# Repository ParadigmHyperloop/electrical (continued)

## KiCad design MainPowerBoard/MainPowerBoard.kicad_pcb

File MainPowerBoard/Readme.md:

# Main Power Board
This board provides approriate conversion of power from 120/240VAC and 37V nominal battery packs and distribution to both 24V and 5V system loads (all loads).

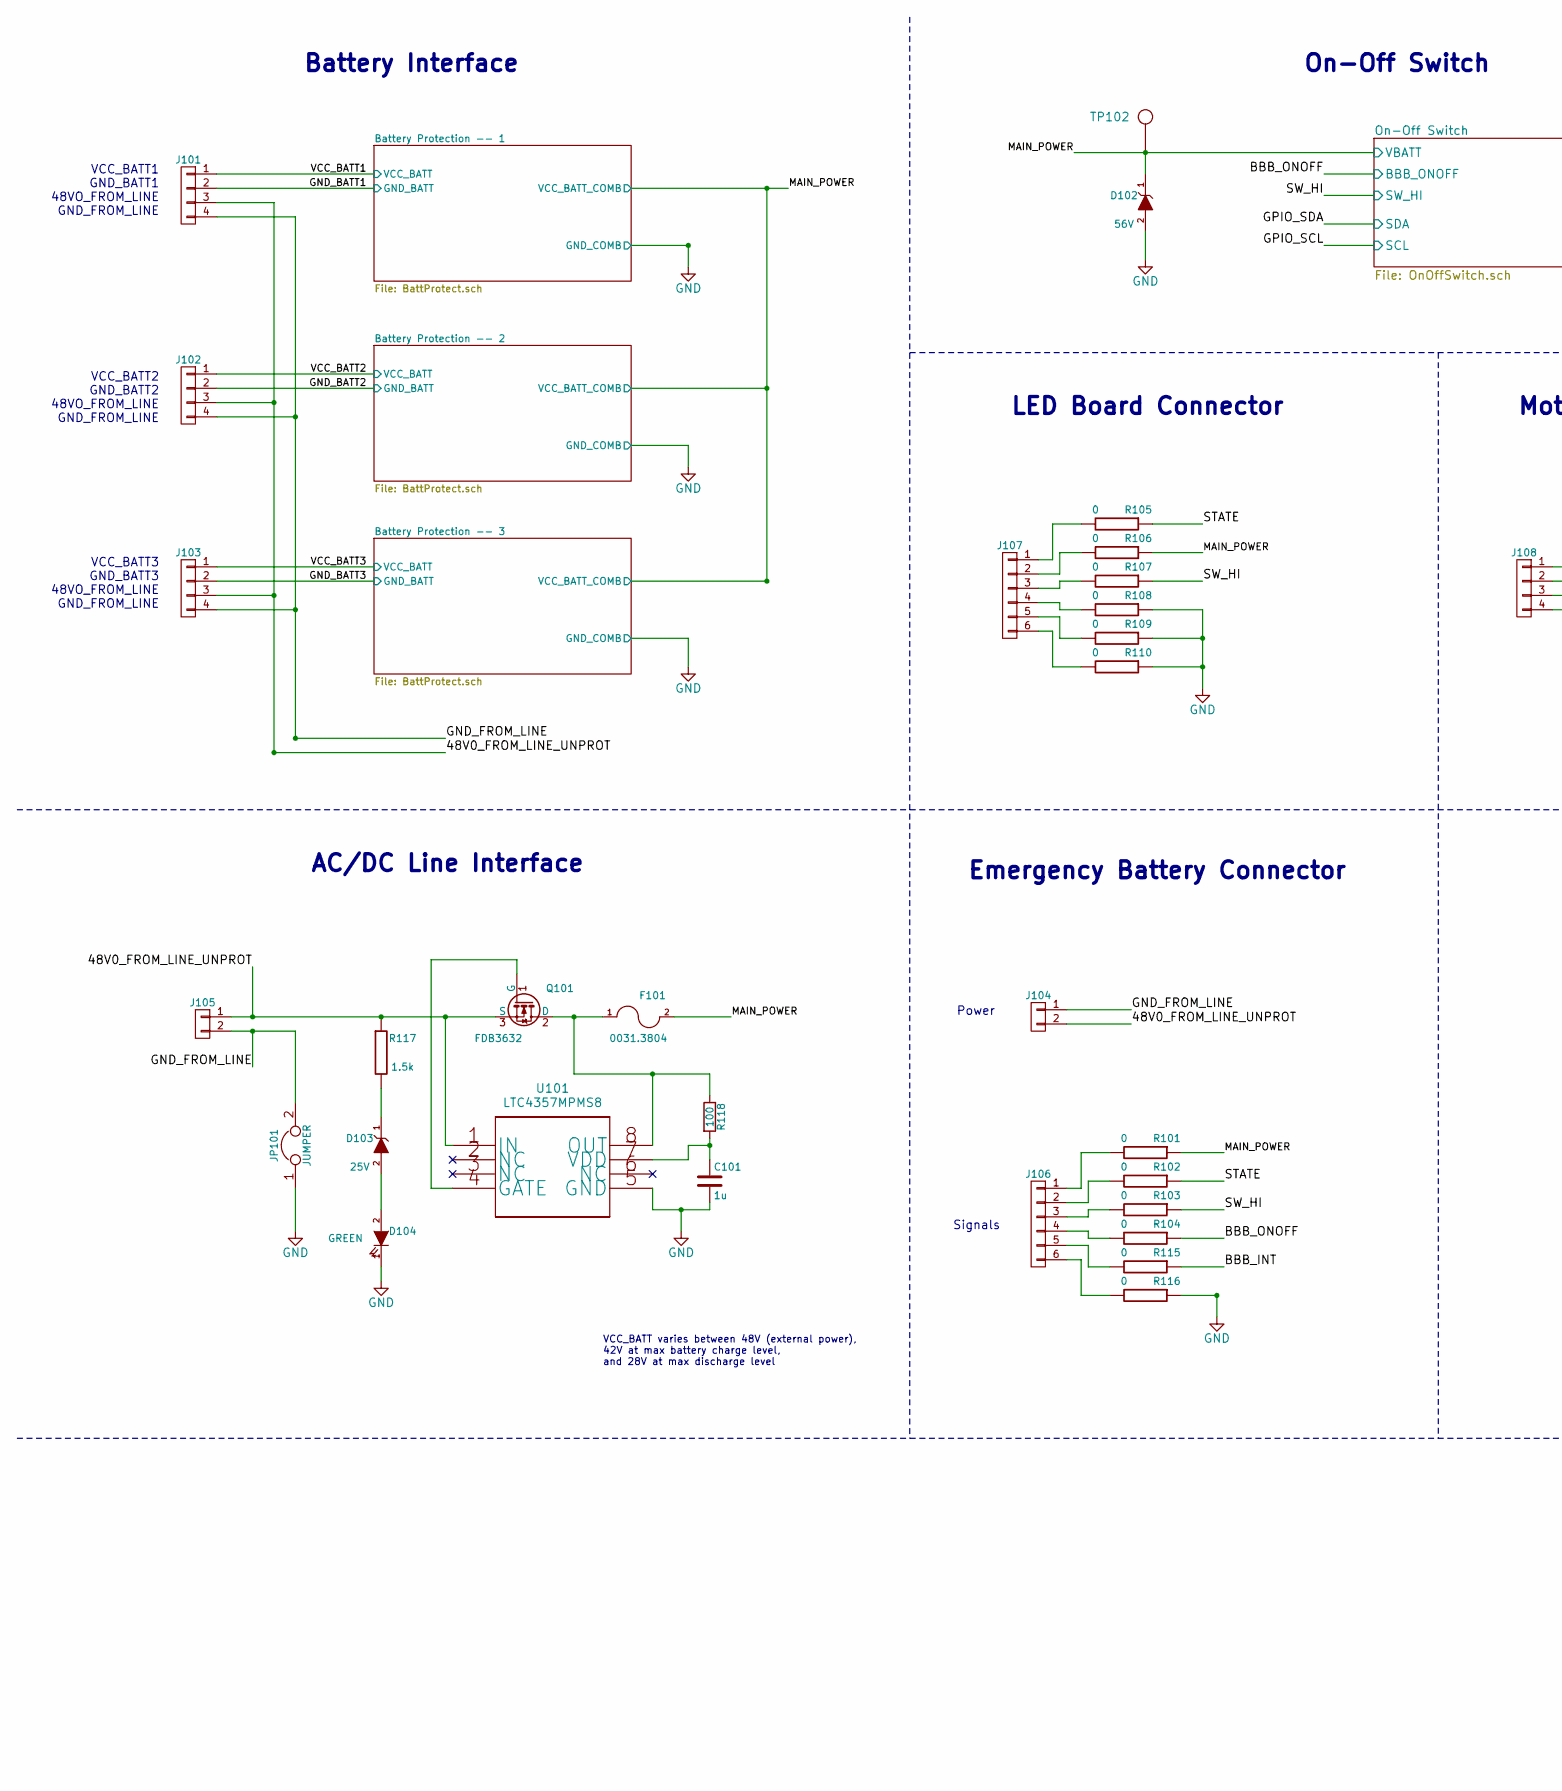
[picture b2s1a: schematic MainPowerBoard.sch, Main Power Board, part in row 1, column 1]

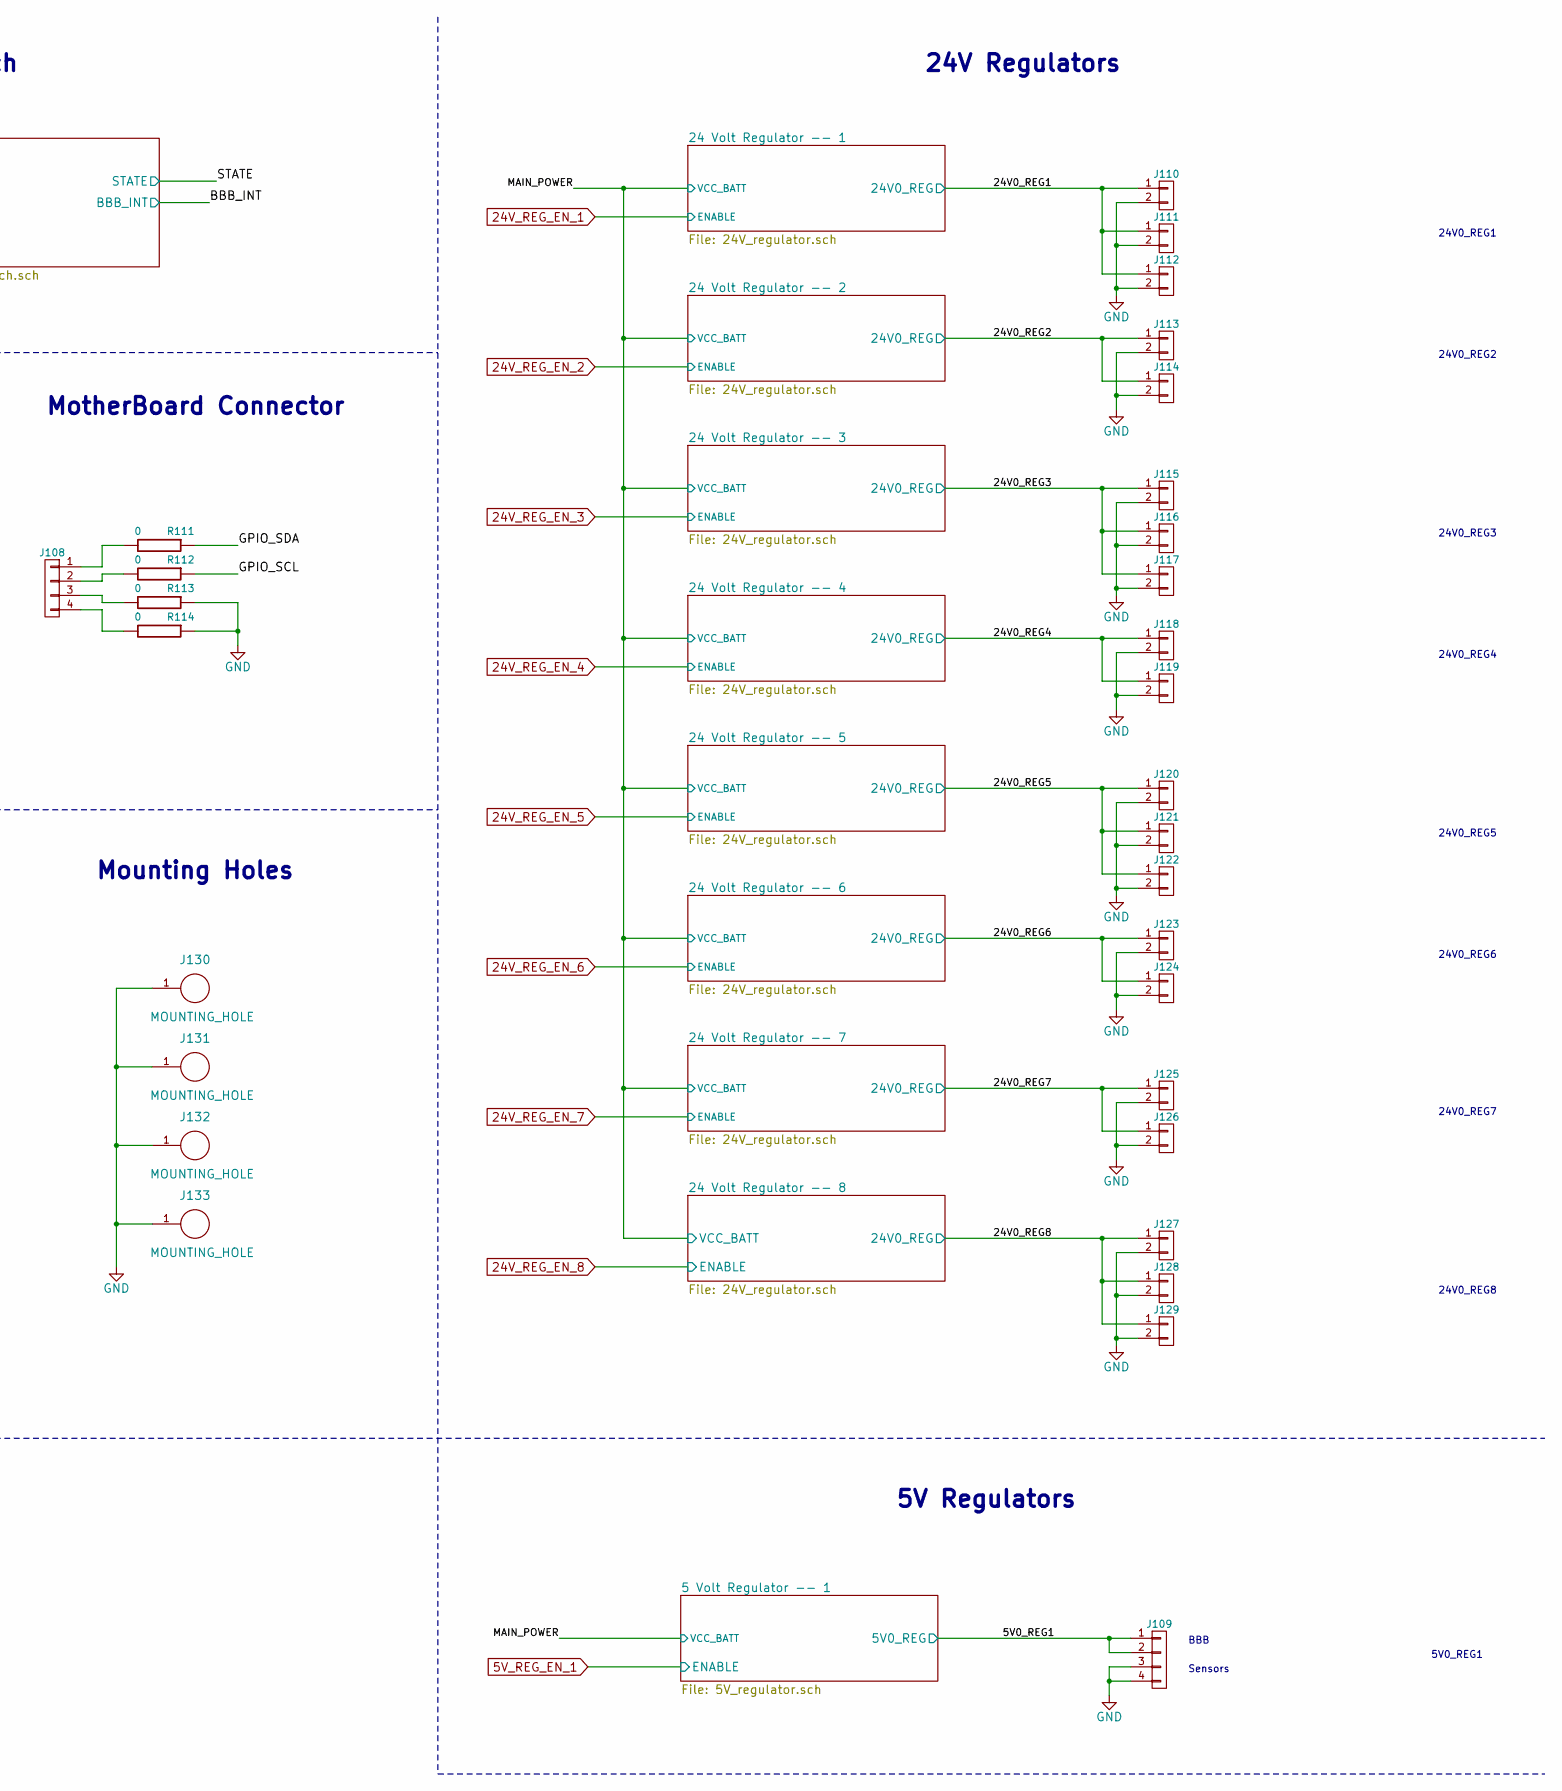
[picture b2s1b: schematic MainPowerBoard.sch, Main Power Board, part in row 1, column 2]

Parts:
C101: 1u; C_0805_HandSoldering; Voltage Rating 100V; Mfg. PN GRJ21BC72A105KE11L; DigiKey PN 490-10918-1-ND
D102: 56V; SMB_Handsoldering; Mfg. PN SMBJ5370B-TP; DigiKey PN SMBJ5370B-TPMSCT-ND
D103: 25V; SOD-123; Mfg. PN MMSZ5253BT1G; DigiKey PN MMSZ5253BT1GOSCT-ND
D104: GREEN; LED_1206; Mfg. PN APT3216LZGCK; DigiKey PN 754-1944-1-ND
F101: 0031.3804; SCHURTER_0031_3804_FUSE; Mfg. PN 0031.3804; DigiKey PN 486-1754-ND
J101, J102, J103, J108, J109: CONN_01X04; CONN_PHOENIX_1844236_4PIN_1; Mfg. PN 1844236; DigiKey PN 277-2419-ND
J104, J110, J111, J112, J113, J114, J115, J116, J117, J118, J119, J120, J121, J122, J123, J124, J125, J126, J127, J128, J129: CONN_01X02; CONN_PHOENIX_1844210_2PIN; Mfg. PN 1844210; DigiKey PN 277-2416-ND
J105: CONN_01X02; CONN_PHOENIX_1720466_2PIN; Mfg. PN 1720466; DigiKey PN 277-6070-ND
J106, J107: CONN_01X06; CONN_PHOENIX_1844252_6PIN; Mfg. PN 1844252; Digikey PN 277-2427-ND
J130, J131, J132, J133: MOUNTING_HOLE; MountingHole_5.5mm_Pad_Via
JP101: JUMPER; R_2512_HandSoldering; Mfg. PN HCJ2512ZT0R00; DigiKey PN HCJ2512ZT0R00CT-ND
Q101: FDB3632; TO-263-2; Mfg. PN FDB3632; Digikey PN FDB3632CT-ND
R101, R102, R103, R104, R105, R106, R107, R108, R109, R110, R111, R112, R113, R114, R115, R116: 0; R_1206_HandSoldering; Mfg. PN RC1206JR-070RL; DigiKey PN 311-0.0ERCT-ND
R117: 1.5k; R_1206_HandSoldering; Mfg. PN ERJ-P08J152V; DigiKey PN P1.5KALCT-ND
R118: 100; R_0603_HandSoldering; Power Rating 3.9W; Mfg. PN RCP0603W100RGEB; DigiKey PN 541-2653-1-ND
TP102: Testpoint; TP_SMT_Keystone; Mfg. PN 5018; DigiKey PN 36-5018CT-ND
U101: LTC4357MPMS8; MSOP-8_3x3mm_Pitch0.65mm; Mfg. PN LTC4357HMS8#PBF; DigiKey PN LTC4357HMS8#PBF-ND

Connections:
/5V0_REG1: J109.1, J109.2; also elsewhere on the board
/24V0_REG1: J110.1, J111.1, J112.1; also elsewhere on the board
/24V0_REG2: J113.1, J114.1; also elsewhere on the board
/24V0_REG3: J115.1, J116.1, J117.1; also elsewhere on the board
/24V0_REG4: J118.1, J119.1; also elsewhere on the board
/24V0_REG5: J120.1, J121.1, J122.1; also elsewhere on the board
/24V0_REG6: J123.1, J124.1; also elsewhere on the board
/24V0_REG7: J125.1, J126.1; also elsewhere on the board
/24V0_REG8: J127.1, J128.1, J129.1; also elsewhere on the board
/48V0_FROM_LINE_UNPROT: J101.3, J102.3, J103.3, J104.2, J105.1, Q101.3 (S), R117.1, U101.1 (IN)
/BBB_INT: R115.1; also elsewhere on the board
/BBB_ONOFF: R104.1; also elsewhere on the board
/GND_FROM_LINE: J101.4, J102.4, J103.4, J104.1, J105.2, JP101.2
/GPIO_SCL: R112.1; also elsewhere on the board
/GPIO_SDA: R111.1; also elsewhere on the board
/MAIN_POWER: D102.1 (A), F101.2, R101.1, R106.1, TP102.~; also elsewhere on the board
/STATE: R102.1, R105.1; also elsewhere on the board
/SW_HI: R103.1, R107.1; also elsewhere on the board
/VCC_BATT1: J101.1; also elsewhere on the board
/VCC_BATT2: J102.1; also elsewhere on the board
/VCC_BATT3: J103.1; also elsewhere on the board
GND: C101.2, D102.2 (K), D104.1 (A), J101.2, J102.2, J103.2, J109.3, J109.4, J110.2, J111.2, J112.2, J113.2, J114.2, J115.2, J116.2, J117.2, J118.2, J119.2, J120.2, J121.2, J122.2, J123.2, J124.2, J125.2, J126.2, J127.2, J128.2, J129.2, J130.1, J131.1, J132.1, J133.1, JP101.1, R108.1, R109.1, R110.1, R113.1, R114.1, R116.1, U101.5 (GND); also elsewhere on the board
unnamed: C101.1, R118.2, U101.7 (VDD)
unnamed: D103.1 (A), R117.2
unnamed: D103.2 (K), D104.2 (K)
unnamed: F101.1, Q101.2 (D), R118.1, U101.8 (OUT)
unnamed: J106.1, R101.2
unnamed: J106.2, R102.2
unnamed: J106.3, R103.2
unnamed: J106.4, R104.2
unnamed: J106.5, R115.2
unnamed: J106.6, R116.2
unnamed: J107.1, R105.2
unnamed: J107.2, R106.2
unnamed: J107.3, R107.2
unnamed: J107.4, R108.2
unnamed: J107.5, R109.2
unnamed: J107.6, R110.2
unnamed: J108.1, R111.2
unnamed: J108.2, R112.2
unnamed: J108.3, R113.2
unnamed: J108.4, R114.2
unnamed: Q101.1 (G), U101.4 (GATE)

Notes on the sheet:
24V Regulators
5V Regulators
Battery Interface
VCC_BATT varies between 48V (external power), 42V at max battery charge level, and 28V at max discharge level
Power
Signals
24V0_REG1
24V0_REG2
24V0_REG3
24V0_REG4
24V0_REG5
24V0_REG6
24V0_REG7
5V0_REG1
BBB
VCC_BATT1 GND_BATT1 48VO_FROM_LINE GND_FROM_LINE
VCC_BATT2 GND_BATT2 48VO_FROM_LINE GND_FROM_LINE
VCC_BATT3 GND_BATT3 48VO_FROM_LINE GND_FROM_LINE
On-Off Switch
LED Board Connector
MotherBoard Connector
AC/DC Line Interface
Emergency Battery Connector
Mounting Holes
Sensors
24V0_REG8

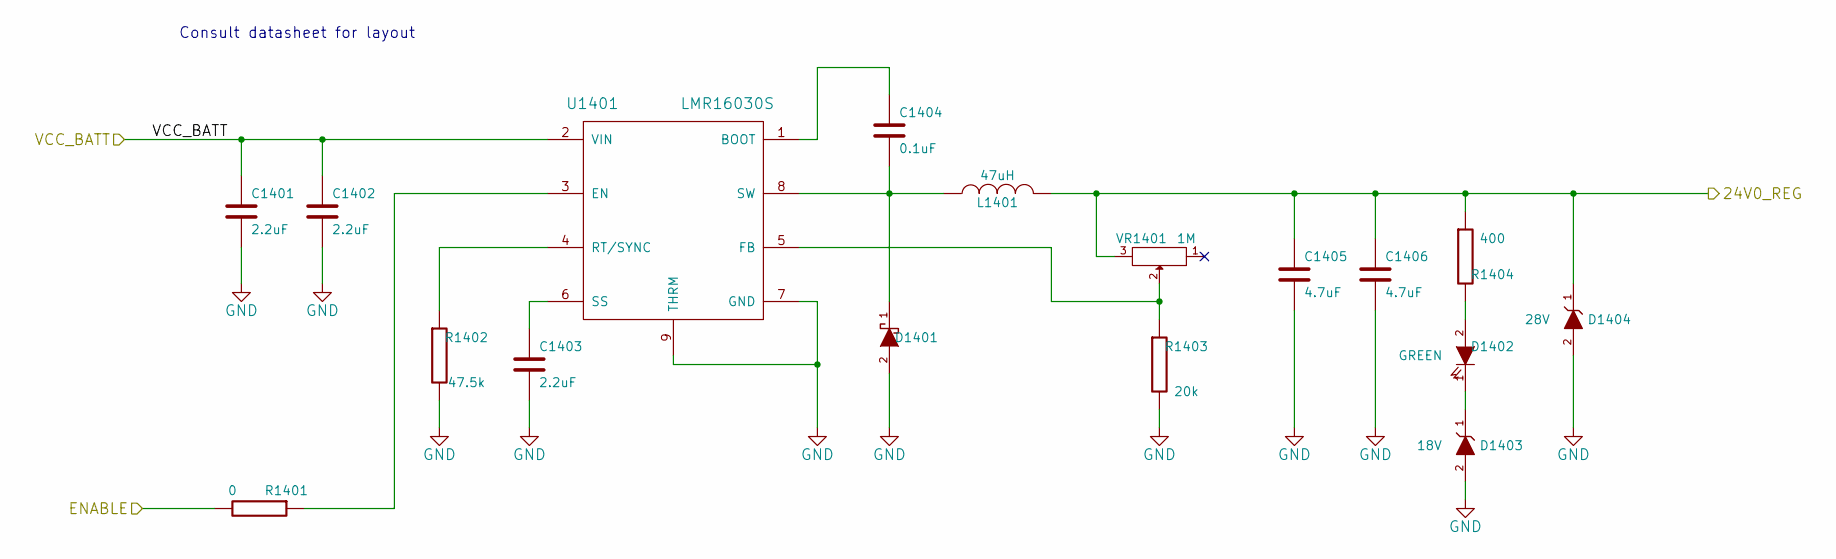
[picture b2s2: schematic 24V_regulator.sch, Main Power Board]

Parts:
C201, C202: 2.2uF; C_1210_HandSoldering; Mfg. PN C3225X7R2A225K230AB; DigiKey PN 445-4497-1-ND
C203: 2.2uF; R_0805_HandSoldering; Mfg. PN C2012C0G1E153J085AA; DigiKey PN 445-2673-1-ND
C204: 0.1uF; R_1206_HandSoldering; Mfg. PN C3225X7R2A225K230AB; DigiKey PN 445-2521-1-ND
C205, C206: 4.7uF; C_1206_HandSoldering; Mfg. PN C3225X7R2A225K230AB; DigiKey PN 490-6521-1-ND
D201: DIODESCH; SMA_Handsoldering; Mfg. PN SK310A-TP; DigiKey PN SK310A-TPCT-ND
D202: GREEN; LED_1206; Mfg. PN APT3216LZGCK; DigiKey PN 754-1944-1-ND
D203: 18V; SMA_Handsoldering; Mfg. PN 1SMA5931BT3G; DigiKey PN 1SMA5931BT3GOSCT-ND
D204: 28V; SMB_Handsoldering; Mfg. PN SMBJ5362B-TP; DigiKey PN SMBJ5362B-TPMSCT-ND
L201: 47uH; 47uIND_CDRH127_LDNP-470MC_SUMIDA_heatsink; Mfg. PN CDRH127/LDNP-470MC; DigiKey PN 308-1339-1-ND
R201: 0; R_1206_HandSoldering; Mfg. PN RC1206JR-070RL; DigiKey PN 311-0.0ERCT-ND
R202: 47.5k; R_1206_HandSoldering; Mfg. PN ERJ-8ENF4752V; DigiKey PN P47.5KFCT-ND
R203: 20k; R_1206_HandSoldering; Mfg. PN CRCW080545K3FKEA; DigiKey PN 541-20.0KFCT-ND
R204: 400; R_1206_HandSoldering; Mfg. PN ERJ-8ENF4020V; DigiKey PN P402FCT-ND
U201: LMR16030S; LMR16030S_8-PowerSOIC_TI; Mfg. PN LMR16030SDDA; DigiKey PN 296-44514-5-ND
VR201: 1M; BOURNS_MULTITURNPOT_3299W; Mfg. PN 3299W-1-105LF; DigiKey PN 3299W-105LF-ND

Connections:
24V_REG_EN_1: R201.2; also elsewhere on the board
/24V0_REG1: C205.1, C206.1, D204.1 (A), L201.2, R204.1, VR201.3; also elsewhere on the board
/MAIN_POWER: C201.1, C202.1, U201.2 (VIN); also elsewhere on the board
GND: C201.2, C202.2, C203.2, C205.2, C206.2, D201.2 (K), D203.2 (K), D204.2 (K), R202.2, R203.2, U201.7 (GND), U201.9 (THRM); also elsewhere on the board
unnamed: C203.1, U201.6 (SS)
unnamed: C204.1, U201.1 (BOOT)
unnamed: C204.2, D201.1 (A), L201.1, U201.8 (SW)
unnamed: D202.1 (A), D203.1 (A)
unnamed: D202.2 (K), R204.2
unnamed: R201.1, U201.3 (EN)
unnamed: R202.1, U201.4 (RT/SYNC)
unnamed: R203.1, U201.5 (FB), VR201.2

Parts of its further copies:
C801, C802, C901, C902, C1001, C1002, C1101, C1102, C1201, C1202, C1301, C1302, C1401, C1402: 2.2uF; C_1210_HandSoldering; Mfg. PN C3225X7R2A225K230AB; DigiKey PN 445-4497-1-ND
C803, C903, C1003, C1103, C1203, C1303, C1403: 2.2uF; R_0805_HandSoldering; Mfg. PN C2012C0G1E153J085AA; DigiKey PN 445-2673-1-ND
C804, C904, C1004, C1104, C1204, C1304, C1404: 0.1uF; R_1206_HandSoldering; Mfg. PN C3225X7R2A225K230AB; DigiKey PN 445-2521-1-ND
C805, C806, C905, C906, C1005, C1006, C1105, C1106, C1205, C1206, C1305, C1306, C1405, C1406: 4.7uF; C_1206_HandSoldering; Mfg. PN C3225X7R2A225K230AB; DigiKey PN 490-6521-1-ND
D801, D901, D1001, D1101, D1201, D1301, D1401: DIODESCH; SMA_Handsoldering; Mfg. PN SK310A-TP; DigiKey PN SK310A-TPCT-ND
D802, D902, D1002, D1102, D1202, D1302, D1402: GREEN; LED_1206; Mfg. PN APT3216LZGCK; DigiKey PN 754-1944-1-ND
D803, D903, D1003, D1103, D1203, D1303, D1403: 18V; SMA_Handsoldering; Mfg. PN 1SMA5931BT3G; DigiKey PN 1SMA5931BT3GOSCT-ND
D804, D904, D1004, D1104, D1204, D1304, D1404: 28V; SMB_Handsoldering; Mfg. PN SMBJ5362B-TP; DigiKey PN SMBJ5362B-TPMSCT-ND
L801, L901, L1001, L1101, L1201, L1301, L1401: 47uH; 47uIND_CDRH127_LDNP-470MC_SUMIDA_heatsink; Mfg. PN CDRH127/LDNP-470MC; DigiKey PN 308-1339-1-ND
R801, R901, R1001, R1101, R1201, R1301, R1401: 0; R_1206_HandSoldering; Mfg. PN RC1206JR-070RL; DigiKey PN 311-0.0ERCT-ND
R802, R902, R1002, R1102, R1202, R1302, R1402: 47.5k; R_1206_HandSoldering; Mfg. PN ERJ-8ENF4752V; DigiKey PN P47.5KFCT-ND
R803, R903, R1003, R1103, R1203, R1303, R1403: 20k; R_1206_HandSoldering; Mfg. PN CRCW080545K3FKEA; DigiKey PN 541-20.0KFCT-ND
R804, R904, R1004, R1104, R1204, R1304, R1404: 400; R_1206_HandSoldering; Mfg. PN ERJ-8ENF4020V; DigiKey PN P402FCT-ND
U801, U901, U1001, U1101, U1201, U1301, U1401: LMR16030S; LMR16030S_8-PowerSOIC_TI; Mfg. PN LMR16030SDDA; DigiKey PN 296-44514-5-ND
VR801, VR901, VR1001, VR1101, VR1201, VR1301, VR1401: 1M; BOURNS_MULTITURNPOT_3299W; Mfg. PN 3299W-1-105LF; DigiKey PN 3299W-105LF-ND

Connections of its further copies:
24V_REG_EN_2: R801.2; also elsewhere on the board
24V_REG_EN_3: R901.2; also elsewhere on the board
24V_REG_EN_4: R1001.2; also elsewhere on the board
24V_REG_EN_5: R1101.2; also elsewhere on the board
24V_REG_EN_6: R1201.2; also elsewhere on the board
24V_REG_EN_7: R1301.2; also elsewhere on the board
24V_REG_EN_8: R1401.2; also elsewhere on the board
/24V0_REG2: C805.1, C806.1, D804.1 (A), L801.2, R804.1, VR801.3; also elsewhere on the board
/24V0_REG3: C905.1, C906.1, D904.1 (A), L901.2, R904.1, VR901.3; also elsewhere on the board
/24V0_REG4: C1005.1, C1006.1, D1004.1 (A), L1001.2, R1004.1, VR1001.3; also elsewhere on the board
/24V0_REG5: C1105.1, C1106.1, D1104.1 (A), L1101.2, R1104.1, VR1101.3; also elsewhere on the board
/24V0_REG6: C1205.1, C1206.1, D1204.1 (A), L1201.2, R1204.1, VR1201.3; also elsewhere on the board
/24V0_REG7: C1305.1, C1306.1, D1304.1 (A), L1301.2, R1304.1, VR1301.3; also elsewhere on the board
/24V0_REG8: C1405.1, C1406.1, D1404.1 (A), L1401.2, R1404.1, VR1401.3; also elsewhere on the board
/MAIN_POWER: C801.1, C802.1, C901.1, C902.1, C1001.1, C1002.1, C1101.1, C1102.1, C1201.1, C1202.1, C1301.1, C1302.1, C1401.1, C1402.1, U801.2 (VIN), U901.2 (VIN), U1001.2 (VIN), U1101.2 (VIN), U1201.2 (VIN), U1301.2 (VIN), U1401.2 (VIN); also elsewhere on the board
GND: C801.2, C802.2, C803.2, C805.2, C806.2, C901.2, C902.2, C903.2, C905.2, C906.2, C1001.2, C1002.2, C1003.2, C1005.2, C1006.2, C1101.2, C1102.2, C1103.2, C1105.2, C1106.2, C1201.2, C1202.2, C1203.2, C1205.2, C1206.2, C1301.2, C1302.2, C1303.2, C1305.2, C1306.2, C1401.2, C1402.2, C1403.2, C1405.2, C1406.2, D801.2 (K), D803.2 (K), D804.2 (K), D901.2 (K), D903.2 (K), D904.2 (K), D1001.2 (K), D1003.2 (K), D1004.2 (K), D1101.2 (K), D1103.2 (K), D1104.2 (K), D1201.2 (K), D1203.2 (K), D1204.2 (K), D1301.2 (K), D1303.2 (K), D1304.2 (K), D1401.2 (K), D1403.2 (K), D1404.2 (K), R802.2, R803.2, R902.2, R903.2, R1002.2, R1003.2, R1102.2, R1103.2, R1202.2, R1203.2, R1302.2, R1303.2, R1402.2, R1403.2, U801.7 (GND), U801.9 (THRM), U901.7 (GND), U901.9 (THRM), U1001.7 (GND), U1001.9 (THRM), U1101.7 (GND), U1101.9 (THRM), U1201.7 (GND), U1201.9 (THRM), U1301.7 (GND), U1301.9 (THRM), U1401.7 (GND), U1401.9 (THRM); also elsewhere on the board
unnamed: C803.1, U801.6 (SS)
unnamed: C804.1, U801.1 (BOOT)
unnamed: C804.2, D801.1 (A), L801.1, U801.8 (SW)
unnamed: C903.1, U901.6 (SS)
unnamed: C904.1, U901.1 (BOOT)
unnamed: C904.2, D901.1 (A), L901.1, U901.8 (SW)
unnamed: C1003.1, U1001.6 (SS)
unnamed: C1004.1, U1001.1 (BOOT)
unnamed: C1004.2, D1001.1 (A), L1001.1, U1001.8 (SW)
unnamed: C1103.1, U1101.6 (SS)
unnamed: C1104.1, U1101.1 (BOOT)
unnamed: C1104.2, D1101.1 (A), L1101.1, U1101.8 (SW)
unnamed: C1203.1, U1201.6 (SS)
unnamed: C1204.1, U1201.1 (BOOT)
unnamed: C1204.2, D1201.1 (A), L1201.1, U1201.8 (SW)
unnamed: C1303.1, U1301.6 (SS)
unnamed: C1304.1, U1301.1 (BOOT)
unnamed: C1304.2, D1301.1 (A), L1301.1, U1301.8 (SW)
unnamed: C1403.1, U1401.6 (SS)
unnamed: C1404.1, U1401.1 (BOOT)
unnamed: C1404.2, D1401.1 (A), L1401.1, U1401.8 (SW)
unnamed: D802.1 (A), D803.1 (A)
unnamed: D802.2 (K), R804.2
unnamed: D902.1 (A), D903.1 (A)
unnamed: D902.2 (K), R904.2
unnamed: D1002.1 (A), D1003.1 (A)
unnamed: D1002.2 (K), R1004.2
unnamed: D1102.1 (A), D1103.1 (A)
unnamed: D1102.2 (K), R1104.2
unnamed: D1202.1 (A), D1203.1 (A)
unnamed: D1202.2 (K), R1204.2
unnamed: D1302.1 (A), D1303.1 (A)
unnamed: D1302.2 (K), R1304.2
unnamed: D1402.1 (A), D1403.1 (A)
unnamed: D1402.2 (K), R1404.2
unnamed: R801.1, U801.3 (EN)
unnamed: R802.1, U801.4 (RT/SYNC)
unnamed: R803.1, U801.5 (FB), VR801.2
unnamed: R901.1, U901.3 (EN)
unnamed: R902.1, U901.4 (RT/SYNC)
unnamed: R903.1, U901.5 (FB), VR901.2
unnamed: R1001.1, U1001.3 (EN)
unnamed: R1002.1, U1001.4 (RT/SYNC)
unnamed: R1003.1, U1001.5 (FB), VR1001.2
unnamed: R1101.1, U1101.3 (EN)
unnamed: R1102.1, U1101.4 (RT/SYNC)
unnamed: R1103.1, U1101.5 (FB), VR1101.2
unnamed: R1201.1, U1201.3 (EN)
unnamed: R1202.1, U1201.4 (RT/SYNC)
unnamed: R1203.1, U1201.5 (FB), VR1201.2
unnamed: R1301.1, U1301.3 (EN)
unnamed: R1302.1, U1301.4 (RT/SYNC)
unnamed: R1303.1, U1301.5 (FB), VR1301.2
unnamed: R1401.1, U1401.3 (EN)
unnamed: R1402.1, U1401.4 (RT/SYNC)
unnamed: R1403.1, U1401.5 (FB), VR1401.2

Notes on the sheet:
Consult datasheet for layout

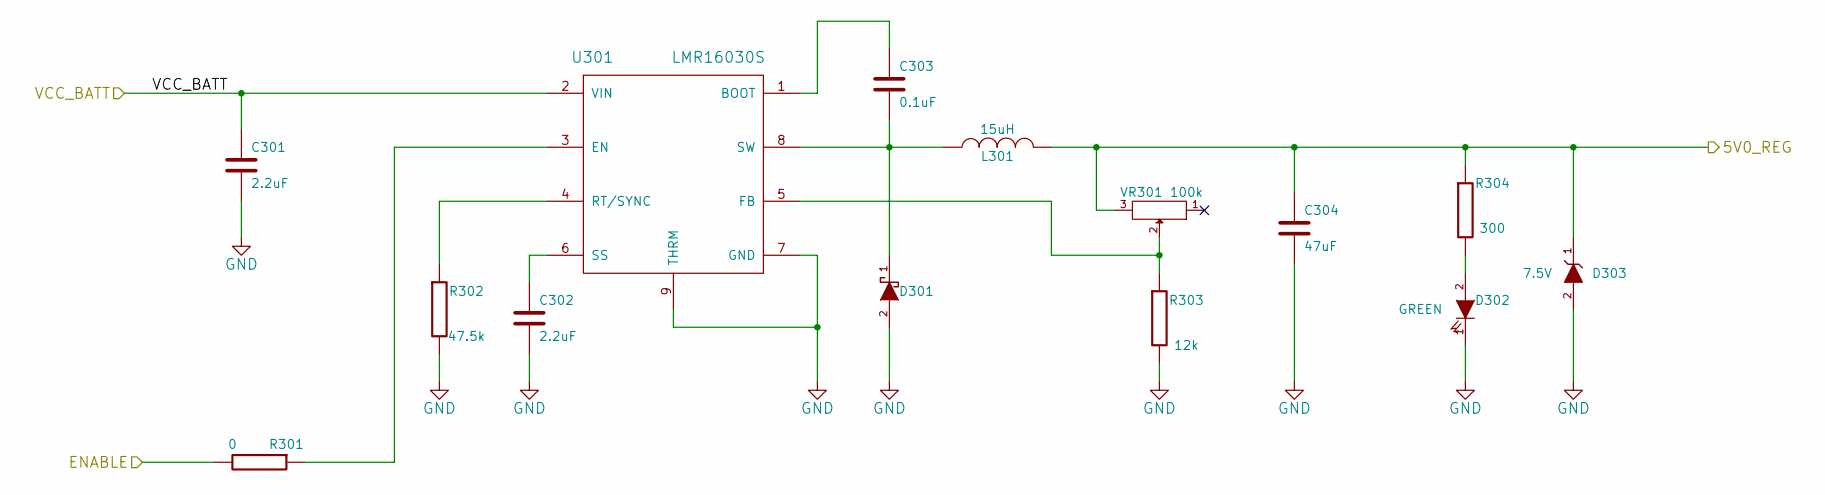
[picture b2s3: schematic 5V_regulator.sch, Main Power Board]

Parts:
C301: 2.2uF; C_1210_HandSoldering; Mfg. PN C3225X7R2A225K230AB; DigiKey PN 445-4497-1-ND
C302: 2.2uF; R_0805_HandSoldering; Mfg. PN C2012C0G1E153J085AA; DigiKey PN 445-2673-1-ND
C303: 0.1uF; R_1206_HandSoldering; Mfg. PN C3225X7R2A225K230AB; DigiKey PN 445-2521-2-ND
C304: 47uF; C_1206_HandSoldering; Mfg. PN C3216X5R1E476M160AC; DigiKey PN 445-8047-1-ND
D301: DIODESCH; SMA_Handsoldering; Mfg. PN SK310A-TP; DigiKey PN SK310A-TPCT-ND
D302: GREEN; LED_1206; Mfg. PN APT3216LZGCK; DigiKey PN 754-1944-1-ND
D303: 7.5V; SMB_Handsoldering; Mfg. PN SMBJ5343B-TP; DigiKey PN SMBJ5343B-TPMSCT-ND
L301: 15uH; 15uIND_SLF10165T-150M3R13PF_BOURNS_heatsink; Mfg. PN SLF10165T-150M3R13PF; DigiKey PN 445-6479-1-ND
R301: 0; R_1206_HandSoldering; Mfg. PN RC1206JR-070RL; DigiKey PN 311-0.0ERCT-ND
R302: 47.5k; R_1206_HandSoldering; Mfg. PN ERJ-8ENF4752V; DigiKey PN P47.5KFCT-ND
R303: 12k; R_1206_HandSoldering; Mfg. PN RC1206FR-0712KL; DigiKey PN 311-12.0KFRCT-ND
R304: 300; SMD-1206_Pol; Mfg. PN ERJ-P08J301V; DigiKey PN P300ALCT-ND
U301: LMR16030S; LMR16030S_8-PowerSOIC_TI; Mfg. PN LMR16030SDDA; DigiKey PN 296-44514-5-ND
VR301: 100k; BOURNS_MULTITURNPOT_3299W; Mfg. PN 3299W-1-104LF; DigiKey PN 3299W-104LF-ND

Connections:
5V_REG_EN_1: R301.2; also elsewhere on the board
/5V0_REG1: C304.1, D303.1 (A), L301.2, R304.1, VR301.3; also elsewhere on the board
/MAIN_POWER: C301.1, U301.2 (VIN); also elsewhere on the board
GND: C301.2, C302.2, C304.2, D301.2 (K), D302.1 (A), D303.2 (K), R302.2, R303.2, U301.7 (GND), U301.9 (THRM); also elsewhere on the board
unnamed: C302.1, U301.6 (SS)
unnamed: C303.1, U301.1 (BOOT)
unnamed: C303.2, D301.1 (A), L301.1, U301.8 (SW)
unnamed: D302.2 (K), R304.2
unnamed: R301.1, U301.3 (EN)
unnamed: R302.1, U301.4 (RT/SYNC)
unnamed: R303.1, U301.5 (FB), VR301.2

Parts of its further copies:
C1401: 2.2uF; C_1210_HandSoldering; Mfg. PN C3225X7R2A225K230AB; DigiKey PN 445-4497-1-ND
C1402: 2.2uF; R_0805_HandSoldering; Mfg. PN C2012C0G1E153J085AA; DigiKey PN 445-2673-1-ND
D1401: DIODESCH; SMA_Handsoldering; Mfg. PN SK310A-TP; DigiKey PN SK310A-TPCT-ND
D1402: GREEN; LED_1206; Mfg. PN APT3216LZGCK; DigiKey PN 754-1944-1-ND
R1401: 0; R_1206_HandSoldering; Mfg. PN RC1206JR-070RL; DigiKey PN 311-0.0ERCT-ND
R1402: 47.5k; R_1206_HandSoldering; Mfg. PN ERJ-8ENF4752V; DigiKey PN P47.5KFCT-ND
U1401: LMR16030S; LMR16030S_8-PowerSOIC_TI; Mfg. PN LMR16030SDDA; DigiKey PN 296-44514-5-ND

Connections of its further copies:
24V_REG_EN_8: R1401.2; also elsewhere on the board
/MAIN_POWER: C1401.1, C1402.1, U1401.2 (VIN); also elsewhere on the board
GND: C1401.2, C1402.2, D1401.2 (K), R1402.2, U1401.7 (GND), U1401.9 (THRM); also elsewhere on the board
unnamed 75: U1401.6 (SS); also elsewhere on the board
unnamed 76: U1401.1 (BOOT); also elsewhere on the board
unnamed 77: D1401.1 (A), U1401.8 (SW); also elsewhere on the board
unnamed 103: D1402.1 (A); also elsewhere on the board
unnamed 104: D1402.2 (K); also elsewhere on the board
unnamed: R1401.1, U1401.3 (EN)
unnamed: R1402.1, U1401.4 (RT/SYNC)
unnamed 156: U1401.5 (FB); also elsewhere on the board

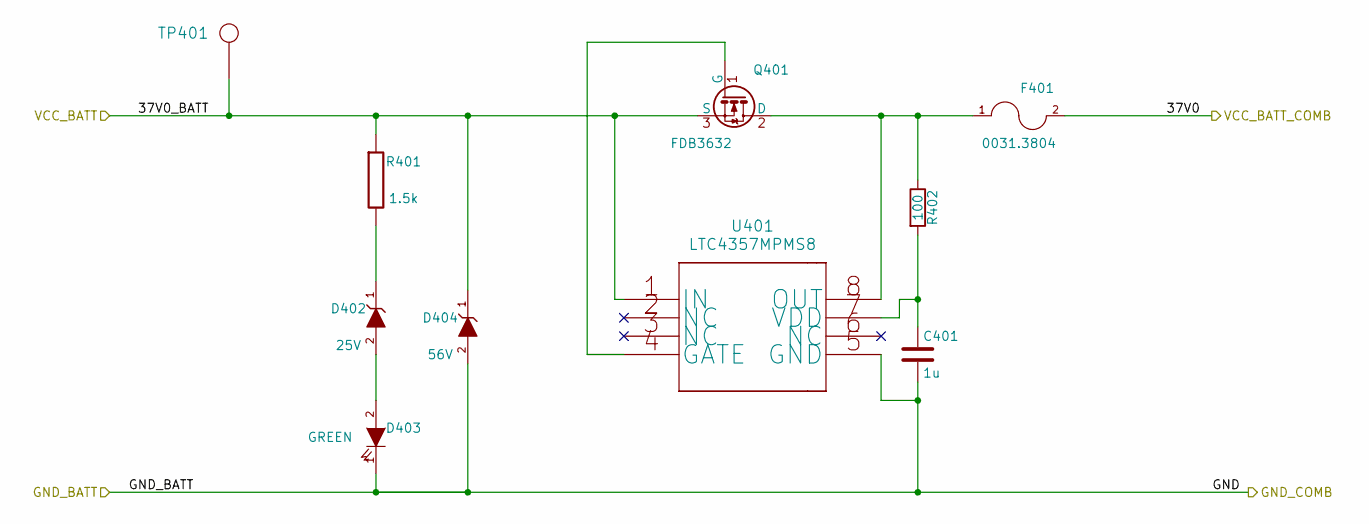
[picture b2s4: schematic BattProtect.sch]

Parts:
C401: 1u; C_0805_HandSoldering; Mfg. PN GRJ21BC72A105KE11L; Digikey PN 490-10918-1-ND
D402: 25V; SOD-123; Mfg. PN MMSZ5253BT1G; DigiKey PN MMSZ5253BT1GOSCT-ND
D403: GREEN; LED_1206; Mfg. PN APT3216LZGCK; DigiKey PN 754-1944-1-ND
D404: 56V; SMB_Handsoldering; Mfg. PN SMBJ5370B-TP; DigiKey PN SMBJ5370B-TPMSCT-ND
F401: 0031.3804; SCHURTER_0031_3804_FUSE; Mfg. PN 0031.3804; DigiKey PN 486-1754-ND
Q401: FDB3632; TO-263-2; Mfg. PN FDB3632; Digikey PN FDB3632CT-ND
R401: 1.5k; R_1206_HandSoldering; Mfg. PN ERJ-P08J152V; DigiKey PN P1.5KALCT-ND
R402: 100; R_0603_HandSoldering; Mfg. PN RCP0603W100RGEB; Digikey PN 541-2653-1-ND
TP401: Testpoint; TP_SMT_Keystone; Mfg. PN 5018; DigiKey PN 36-5018CT-ND
U401: LTC4357MPMS8; MSOP-8_3x3mm_Pitch0.65mm; Mfg. PN LTC4357HMS8#PBF; Digikey PN LTC4357HMS8#PBF-ND

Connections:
/MAIN_POWER: F401.2; also elsewhere on the board
/VCC_BATT1: D404.1 (A), Q401.3 (S), R401.1, TP401.~, U401.1 (IN); also elsewhere on the board
GND: C401.2, D403.1 (A), D404.2 (K), U401.5 (GND); also elsewhere on the board
unnamed: C401.1, R402.2, U401.7 (VDD)
unnamed: D402.1 (A), R401.2
unnamed: D402.2 (K), D403.2 (K)
unnamed: F401.1, Q401.2 (D), R402.1, U401.8 (OUT)
unnamed: Q401.1 (G), U401.4 (GATE)

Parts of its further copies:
C501, C601: 1u; C_0805_HandSoldering; Mfg. PN GRJ21BC72A105KE11L; Digikey PN 490-10918-1-ND
D502, D602: 25V; SOD-123; Mfg. PN MMSZ5253BT1G; DigiKey PN MMSZ5253BT1GOSCT-ND
D503, D603: GREEN; LED_1206; Mfg. PN APT3216LZGCK; DigiKey PN 754-1944-1-ND
D504, D604: 56V; SMB_Handsoldering; Mfg. PN SMBJ5370B-TP; DigiKey PN SMBJ5370B-TPMSCT-ND
F501, F601: 0031.3804; SCHURTER_0031_3804_FUSE; Mfg. PN 0031.3804; DigiKey PN 486-1754-ND
Q501, Q601: FDB3632; TO-263-2; Mfg. PN FDB3632; Digikey PN FDB3632CT-ND
R501, R601: 1.5k; R_1206_HandSoldering; Mfg. PN ERJ-P08J152V; DigiKey PN P1.5KALCT-ND
R502, R602: 100; R_0603_HandSoldering; Mfg. PN RCP0603W100RGEB; Digikey PN 541-2653-1-ND
TP501, TP601: Testpoint; TP_SMT_Keystone; Mfg. PN 5018; DigiKey PN 36-5018CT-ND
U501, U601: LTC4357MPMS8; MSOP-8_3x3mm_Pitch0.65mm; Mfg. PN LTC4357HMS8#PBF; Digikey PN LTC4357HMS8#PBF-ND

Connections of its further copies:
/MAIN_POWER: F501.2, F601.2; also elsewhere on the board
/VCC_BATT2: D604.1 (A), Q601.3 (S), R601.1, TP601.~, U601.1 (IN); also elsewhere on the board
/VCC_BATT3: D504.1 (A), Q501.3 (S), R501.1, TP501.~, U501.1 (IN); also elsewhere on the board
GND: C501.2, C601.2, D503.1 (A), D504.2 (K), D603.1 (A), D604.2 (K), U501.5 (GND), U601.5 (GND); also elsewhere on the board
unnamed: C501.1, R502.2, U501.7 (VDD)
unnamed: C601.1, R602.2, U601.7 (VDD)
unnamed: D502.1 (A), R501.2
unnamed: D502.2 (K), D503.2 (K)
unnamed: D602.1 (A), R601.2
unnamed: D602.2 (K), D603.2 (K)
unnamed: F501.1, Q501.2 (D), R502.1, U501.8 (OUT)
unnamed: F601.1, Q601.2 (D), R602.1, U601.8 (OUT)
unnamed: Q501.1 (G), U501.4 (GATE)
unnamed: Q601.1 (G), U601.4 (GATE)

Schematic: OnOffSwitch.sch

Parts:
C701, C703: C; C_1206_HandSoldering
C702: 10uF; SMD-1206_Pol; Mfg. PN CL31B106MOHNNNE; DigiKey PN 1276-6641-1-ND
D701: RED; LED_1206; Mfg. PN APT3216LSECK/J3-PRV; DigiKey PN 754-1940-1-ND
D702: GREEN; LED_1206; Mfg. PN APT3216LZGCK; DigiKey PN 754-1944-1-ND
R701: 100k; SMD-1206_Pol; Mfg. PN RC1206FR-07100KL; DigiKey PN 311-100KFRCT-ND
R702, R703: 500k; SMD-1206_Pol; Mfg. PN RC1206FR-07499KL; DigiKey PN 311-499KFRCT-ND
R704, R706: 10k; SMD-1206_Pol; Mfg. PN RC1206FR-0710KL; DigiKey PN 311-10.0KFRCT-ND
R705, R709: 300; SMD-1206_Pol; Mfg. PN ERJ-P08J301V; DigiKey PN P300ALCT-ND
R707, R708: 1M; SMD-1206_Pol; Mfg. PN RC1206FR-071ML; DigiKey PN 311-1.00MFRCT-ND
SW701: KS-01Q-01; SW_Eswitch_KS-01Q-01; Mfg. PN KS-01Q-01; DigiKey PN EG4791-ND
U701: AP2204RA-5.0TRG1; Reg_SOT89-3_Diodes_PinNames; Mfg. PN AP2204RA-5.0TRG1; DigiKey PN AP2204RA-5.0TRG1DICT-ND
U702: TLV271IDBVR; SOT-23-5; Mfg. PN TLV271IDBVR; DigiKey PN 296-13371-1-ND
U703: LTC2950-1; LT_LTC2950-1_TSOT-23-8; Mfg. PN LTC2950ITS8-1#TRMPBF; DigiKey PN LTC2950ITS8-1#TRMPBFCT-ND
U704: TLC393; SOIC-8_3.9x4.9mm_Pitch1.27mm; Mfg. PN TLC393CDR; DigiKey PN 296-1329-1-ND
U705: MCP23017; SOIC-28W_7.5x17.9mm_Pitch1.27mm; Mfg. P/N MCP23017T-E/SO; DigiKey P/N MCP23017T-E/SOCT-ND
U706, U707, U708: 74HC11; TSSOP-14_4.4x5mm_Pitch0.65mm; Mfg. P/N 74HC11PW,118; DigiKey P/N 1727-6578-1-ND

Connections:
5V_REG_EN_1: U708.8; also elsewhere on the board
24V_REG_EN_1: U706.12; also elsewhere on the board
24V_REG_EN_2: U706.6; also elsewhere on the board
24V_REG_EN_3: U706.8; also elsewhere on the board
24V_REG_EN_4: U707.12; also elsewhere on the board
24V_REG_EN_5: U707.6; also elsewhere on the board
24V_REG_EN_6: U707.8; also elsewhere on the board
24V_REG_EN_7: U708.12; also elsewhere on the board
24V_REG_EN_8: U708.6; also elsewhere on the board
/BBB_INT: R706.2, U703.5 (~INT), U705.4; also elsewhere on the board
/BBB_ONOFF: R704.2, U702.3 (+); also elsewhere on the board
/GPIO_SCL: U705.12; also elsewhere on the board
/GPIO_SDA: U705.13; also elsewhere on the board
/MAIN_POWER: U701.VI; also elsewhere on the board
/On-Off Switch/5V0: C702.1, D701.2 (K), D702.2 (K), R703.2, R704.1, R706.1, R707.1, U701.VO, U702.5 (V+), U703.1 (VIN), U704.8 (VDD), U705.9, U705.18, U706.5, U706.11, U706.13, U706.14, U707.5, U707.11, U707.13, U707.14, U708.5, U708.11, U708.13, U708.14
/On-Off Switch/5V_REG_1_GPIO: U705.8, U708.10
/On-Off Switch/24V_REG_1_GPIO: U705.28, U706.2
/On-Off Switch/24V_REG_2_GPIO: U705.27, U706.4
/On-Off Switch/24V_REG_3_GPIO: U705.26, U706.10
/On-Off Switch/24V_REG_4_GPIO: U705.25, U707.2
/On-Off Switch/24V_REG_5_GPIO: U705.24, U707.4
/On-Off Switch/24V_REG_6_GPIO: U705.23, U707.10
/On-Off Switch/24V_REG_7_GPIO: U705.22, U708.2
/On-Off Switch/24V_REG_8_GPIO: U705.21, U708.4
/On-Off Switch/BBB_KILL_5V: R702.1, U702.1, U703.8 (~KILL), U705.6
/On-Off Switch/GREEN_NEG: R709.2, U704.1 (1OUT)
/On-Off Switch/RED_NEG: R705.2, U704.7 (2OUT)
/On-Off Switch/VREF: R707.2, R708.1, U704.3 (1IN+), U704.6 (2IN-)
/STATE: R703.1, U703.6 (EN), U704.2 (1IN-), U704.5 (2IN+), U705.2, U706.1, U706.3, U706.9, U707.1, U707.3, U707.9, U708.1, U708.3, U708.9; also elsewhere on the board
/SW_HI: SW701.2, U703.2 (~PB), U705.1; also elsewhere on the board
GND: C701.2, C702.2, C703.2, R701.2, R708.2, SW701.1, U701.GND, U702.2 (V-), U703.4 (GND), U704.4 (GND), U705.10, U705.15, U705.16, U705.17, U706.7, U707.7, U708.7; also elsewhere on the board
unnamed: C701.1, U703.3 (ONT)
unnamed: C703.1, U703.7 (OFFT)
unnamed: D701.1 (A), R705.1
unnamed: D702.1 (A), R709.1
unnamed: R701.1, R702.2, U702.4 (-)

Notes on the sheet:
5V Linear Regulator
Voltage Regulator
System Input/Output
Switch
BBB Level Shift
On/Off Switch Controller
BBB_KILL Pull-up
Indicator LEDs
STATE Pull-up
To support indicator LEDs
For test purposes
BBB_INT Pull-up
NOSTUFF
LED Comparator
AND Gate Logic
GPIO Expander (I2C)
